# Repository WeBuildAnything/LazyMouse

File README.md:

# LazyMouse
Based on Arduino library [ESP32 BLE Combo Keyboard & Mouse](https://github.com/blackketter/ESP32-BLE-Combo.git) library by blackketter, which is a fork of T-vK Library.

The IMU sensor uses the [MPU6050 library by Electronic Cats](https://github.com/ElectronicCats/mpu6050.git).

Download and install these libraies before running the code.
# Features
1) Air Mouse with Left and Right Clicks 
2) Vertical and Horizontal Scrolling with Middle Click
3) Volume Control
4) Mute Key
5) Media Control (Play/Pause, Next, Previous)
6) Battery Voltage Sensing and Update every 15 mins

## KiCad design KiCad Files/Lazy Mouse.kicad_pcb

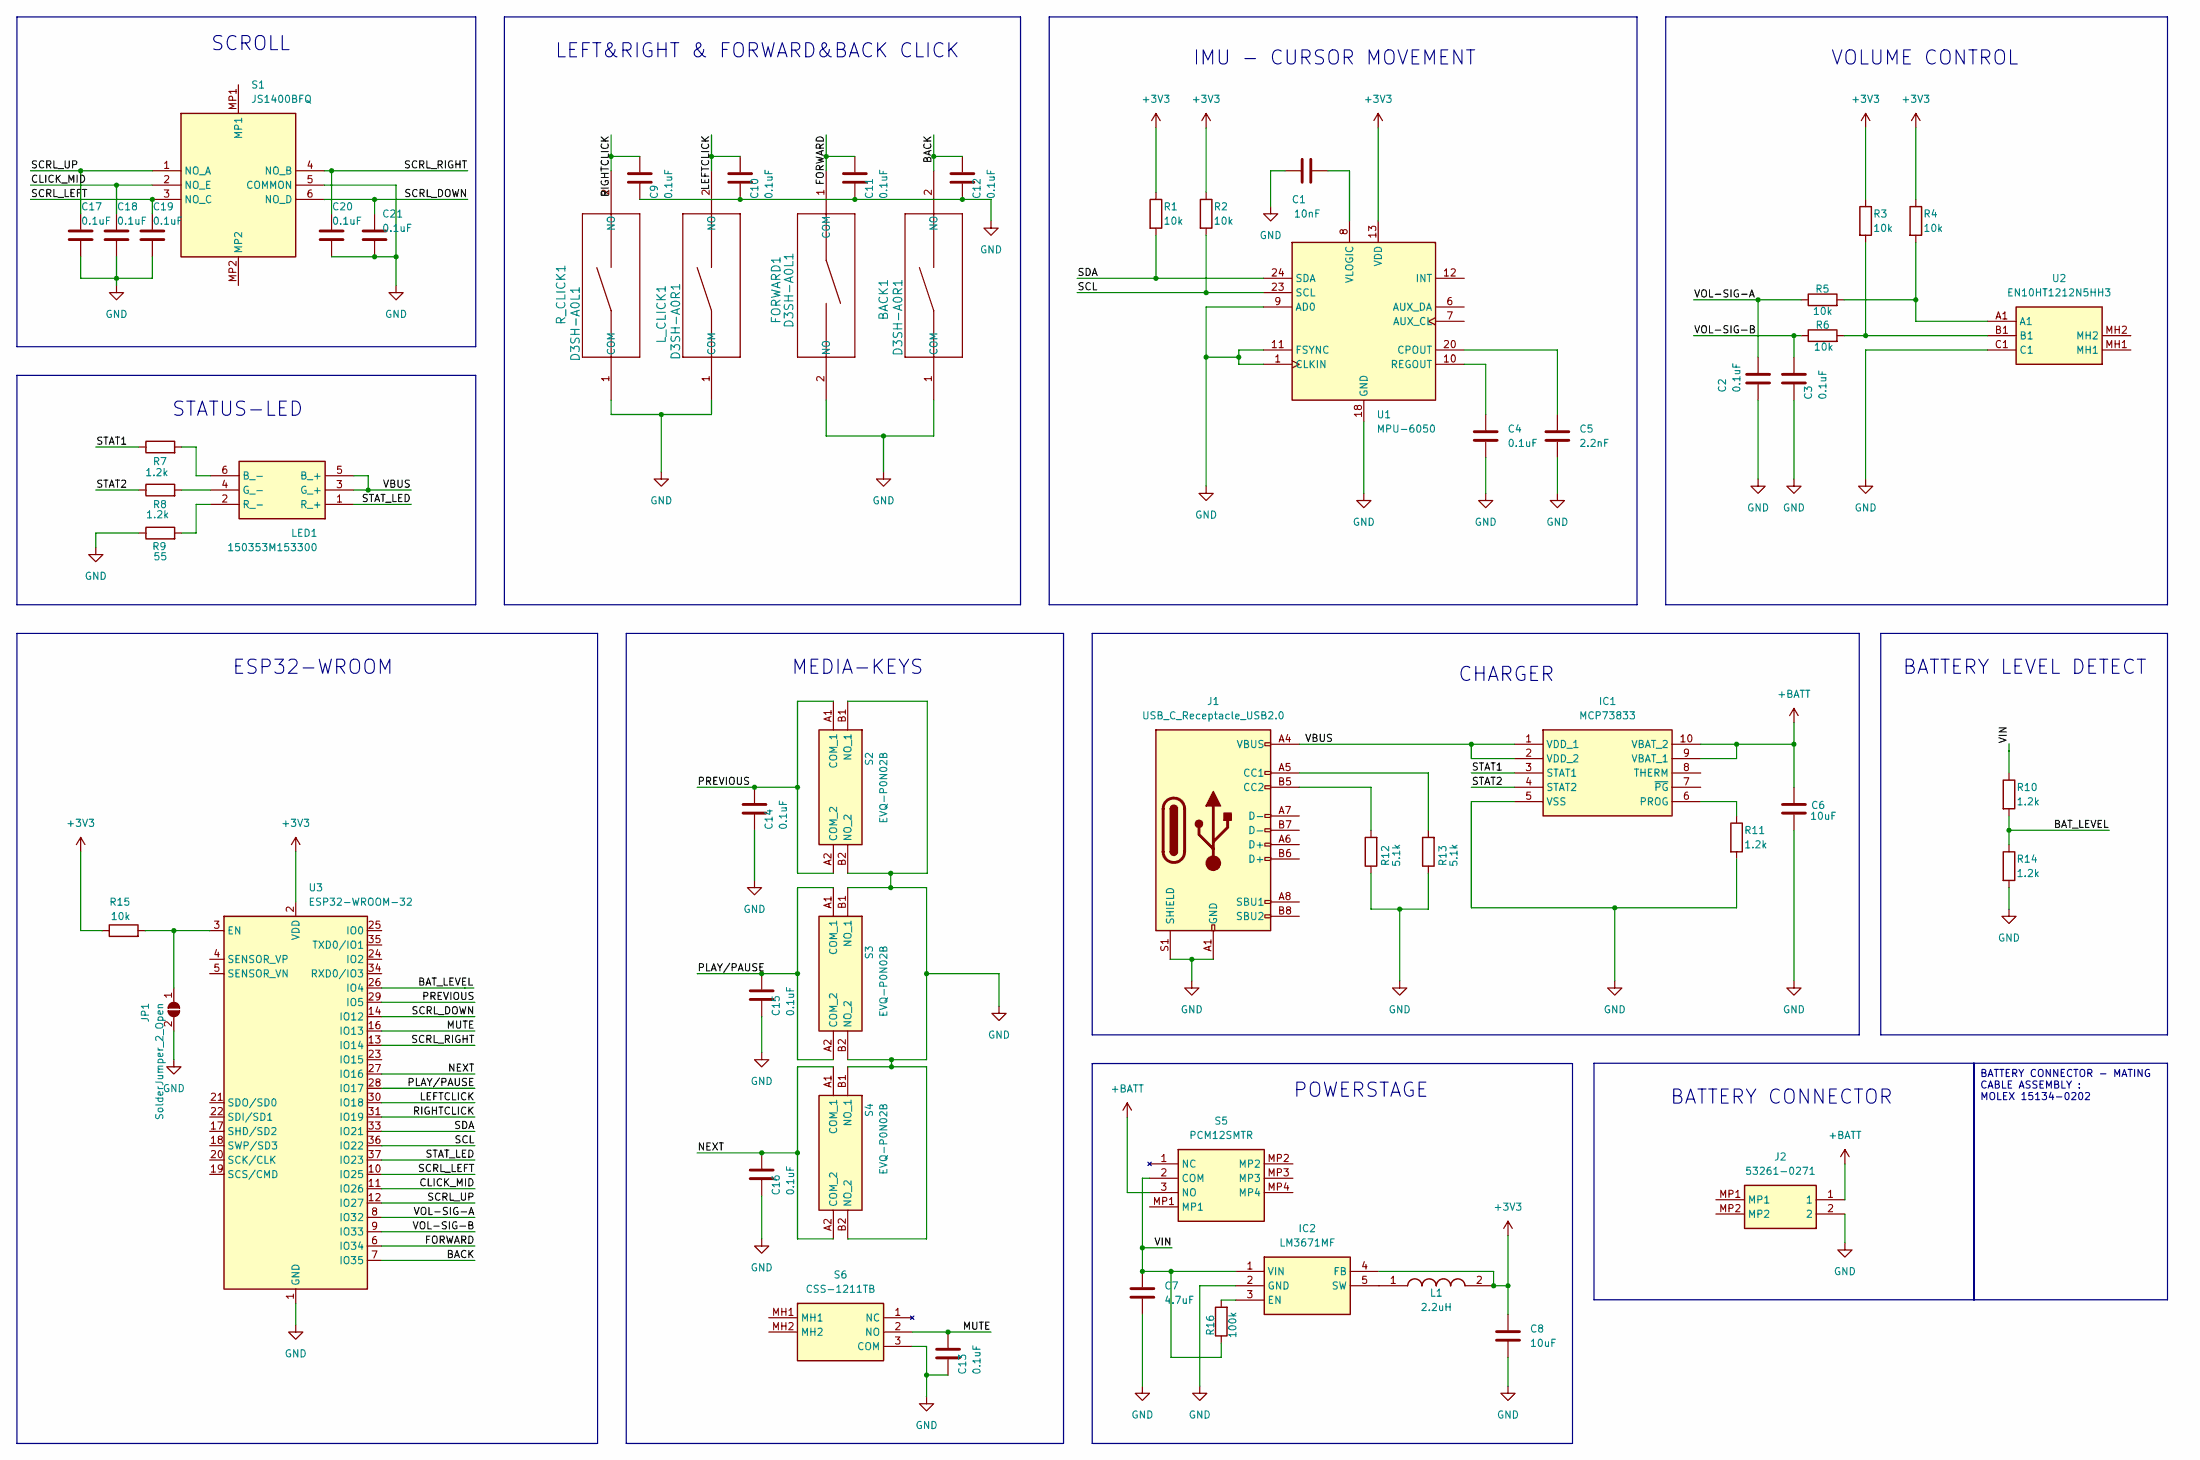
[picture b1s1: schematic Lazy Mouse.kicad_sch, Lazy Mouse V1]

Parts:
BACK1: D3SH-A0R1; D3SH-_0R1
C1: 10nF; C_0603_1608Metric
C2, C3, C4, C9, C10, C11, C12, C13, C14, C15, C16, C17, C18, C19, C20, C21: 0.1uF; C_0603_1608Metric
C5: 2.2nF; C_0603_1608Metric
C6, C8: 10uF; C_0603_1608Metric
C7: 4.7uF; C_0603_1608Metric
FORWARD1: D3SH-A0L1; D3SH-_0L1
IC1: MCP73833; SOP50P490X110-10N; Mouser Part Number 579-MCP73833-FCI/UN
IC2: LM3671MF; SOT95P280X145-5N; Mouser Part Number 926-LM3671MF125NOPB
J1: USB_C_Receptacle_USB2.0; USB_C_Receptacle_GCT_USB4105-xx-A_16P_TopMnt_Horizontal
J2: 53261-0271; 532610271; Mouser Part Number 538-53261-0271
JP1: SolderJumper_2_Open; SolderJumper-2_P1.3mm_Open_RoundedPad1.0x1.5mm
L1: 2.2uH; NRH2412T2R2MNGH; Mouser Part Number 963-NRH2412T2R2MNGH
LED1: 150353M153300; Mouser Part Number 710-150353M153300
L_CLICK1: D3SH-A0R1; D3SH-_0R1
R1, R2, R3, R4, R5, R6, R15: 10k; R_0603_1608Metric
R7, R8, R10, R11, R14: 1.2k; R_0603_1608Metric
R9: 55; R_0603_1608Metric
R12, R13: 5.1k; R_0603_1608Metric
R16: 100k; R_0603_1608Metric
R_CLICK1: D3SH-A0L1; D3SH-_0L1
S1: JS1400BFQ; Mouser Part Number 612-JS1400BFQ
S2, S3, S4: EVQ-P0N02B; EVQP0N02B; Mouser Part Number 667-EVQ-P0N02B
S5: PCM12SMTR; Mouser Part Number 611-PCM12SMTR
S6: CSS-1211TB; CSS1211TB; Manufacturer_Part_Number CSS-1211TB
U1: MPU-6050; InvenSense_QFN-24_4x4mm_P0.5mm
U2: EN10HT1212N5HH3; Mouser Part Number 858-EN10HT1212N5HH3
U3: ESP32-WROOM-32; ESP32-WROOM-32D

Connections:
+3V3: C8.1, IC2.4 (FB), L1.2, R1.1, R2.1, R3.1, R4.1, R15.1, U1.13 (VDD), U3.2 (VDD)
+BATT: C6.2, IC1.9 (VBAT_1), IC1.10 (VBAT_2), J2.1, S5.3 (NO)
/BACK: BACK1.2 (NO), C12.1, U3.7 (IO35)
/BAT_LEVEL: R10.2, R14.1, U3.26 (IO4)
/CLICK_MID: C18.1, S1.2 (NO_E), U3.11 (IO26)
/FORWARD: C11.1, FORWARD1.1 (COM), U3.6 (IO34)
/LEFTCLICK: C10.1, L_CLICK1.2 (NO), U3.30 (IO18)
/MUTE: C13.1, S6.2 (NO), U3.16 (IO13)
/NEXT: C16.1, S4.A1 (COM_1), S4.A2 (COM_2), U3.27 (IO16)
/PLAY/PAUSE: C15.1, S3.A1 (COM_1), S3.A2 (COM_2), U3.28 (IO17)
/PREVIOUS: C14.1, S2.A1 (COM_1), S2.A2 (COM_2), U3.29 (IO5)
/RIGHTCLICK: C9.1, R_CLICK1.2 (NO), U3.31 (IO19)
/SCL: R2.2, U1.23 (SCL), U3.36 (IO22)
/SCRL_DOWN: C21.1, S1.6 (NO_D), U3.14 (IO12)
/SCRL_LEFT: C19.1, S1.3 (NO_C), U3.10 (IO25)
/SCRL_RIGHT: C20.1, S1.4 (NO_B), U3.13 (IO14)
/SCRL_UP: C17.1, S1.1 (NO_A), U3.12 (IO27)
/SDA: R1.2, U1.24 (SDA), U3.33 (IO21)
/STAT1: IC1.3 (STAT1), R7.1
/STAT2: IC1.4 (STAT2), R8.1
/STAT_LED: LED1.1 (R_+), U3.37 (IO23)
/VBUS: IC1.1 (VDD_1), IC1.2 (VDD_2), J1.A4 (VBUS), J1.A9 (VBUS), J1.B4 (VBUS), J1.B9 (VBUS), LED1.3 (G_+), LED1.5 (B_+)
/VIN: C7.1, IC2.1 (VIN), R10.1, R16.1, S5.2 (COM)
/VOL-SIG-A: C2.1, R5.1, U3.8 (IO32)
/VOL-SIG-B: C3.1, R6.1, U3.9 (IO33)
GND: BACK1.1 (COM), C1.1, C2.2, C3.2, C4.2, C5.2, C6.1, C7.2, C8.2, C9.2, C10.2, C11.2, C12.2, C13.2, C14.2, C15.2, C16.2, C17.2, C18.2, C19.2, C20.2, C21.2, FORWARD1.2 (NO), IC1.5 (VSS), IC2.2 (GND), J1.A1 (GND), J1.A12 (GND), J1.B1 (GND), J1.B12 (GND), J1.S1 (SHIELD), J2.2, JP1.2 (B), L_CLICK1.1 (COM), R9.1, R11.2, R12.1, R13.1, R14.2, R_CLICK1.1 (COM), S1.5 (COMMON), S2.B1 (NO_1), S2.B2 (NO_2), S3.B1 (NO_1), S3.B2 (NO_2), S4.B1 (NO_1), S4.B2 (NO_2), S6.3 (COM), U1.1 (CLKIN), U1.9 (AD0), U1.11 (FSYNC), U1.18 (GND), U2.C1, U3.1 (GND), U3.15 (GND), U3.38 (GND), U3.39 (GND); also elsewhere on the board
unnamed: IC1.6 (PROG), R11.1
unnamed: IC2.3 (EN), R16.2
unnamed: IC2.5 (SW), L1.1
unnamed: J1.A5 (CC1), R13.2
unnamed: J1.B5 (CC2), R12.2
unnamed: JP1.1 (A), R15.2, U3.3 (EN)
unnamed: LED1.6 (B_-), R7.2
unnamed: LED1.4 (G_-), R8.2
unnamed: LED1.2 (R_-), R9.2
unnamed: R3.2, R6.2, U2.B1
unnamed: R4.2, R5.2, U2.A1
unnamed: C5.1, U1.20 (CPOUT)
unnamed: C4.1, U1.10 (REGOUT)
unnamed: C1.2, U1.8 (VLOGIC)

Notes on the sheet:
BATTERY CONNECTOR - MATING CABLE ASSEMBLY : MOLEX 15134-0202
VOLUME CONTROL
BATTERY LEVEL DETECT
MEDIA-KEYS
STATUS-LED
LEFT&RIGHT & FORWARD&BACK CLICK
BATTERY CONNECTOR
IMU - CURSOR MOVEMENT
POWERSTAGE
CHARGER
ESP32-WROOM
SCROLL

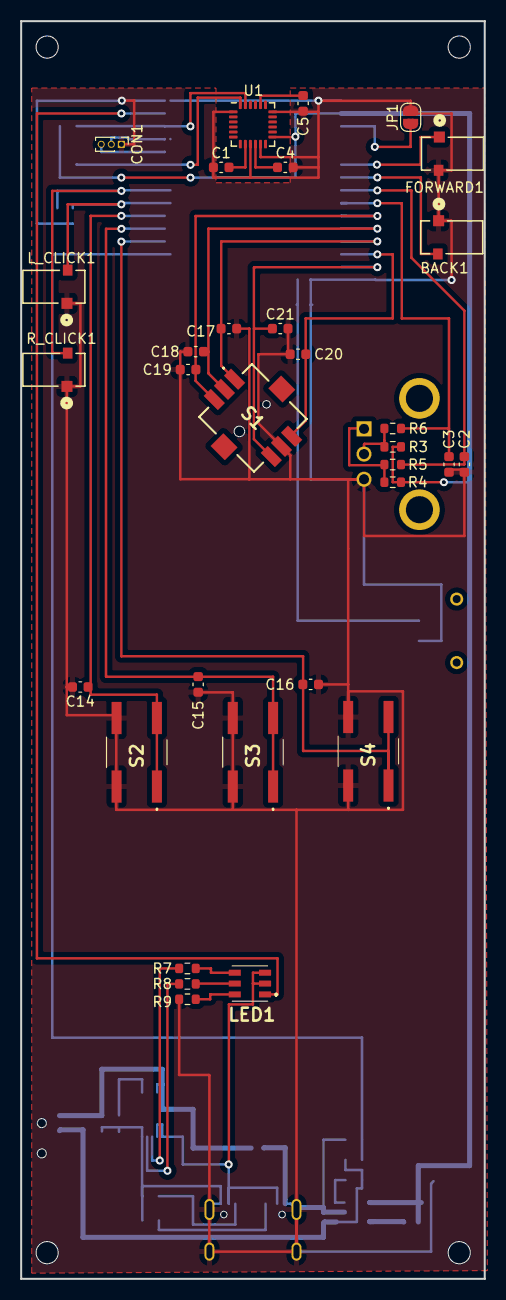
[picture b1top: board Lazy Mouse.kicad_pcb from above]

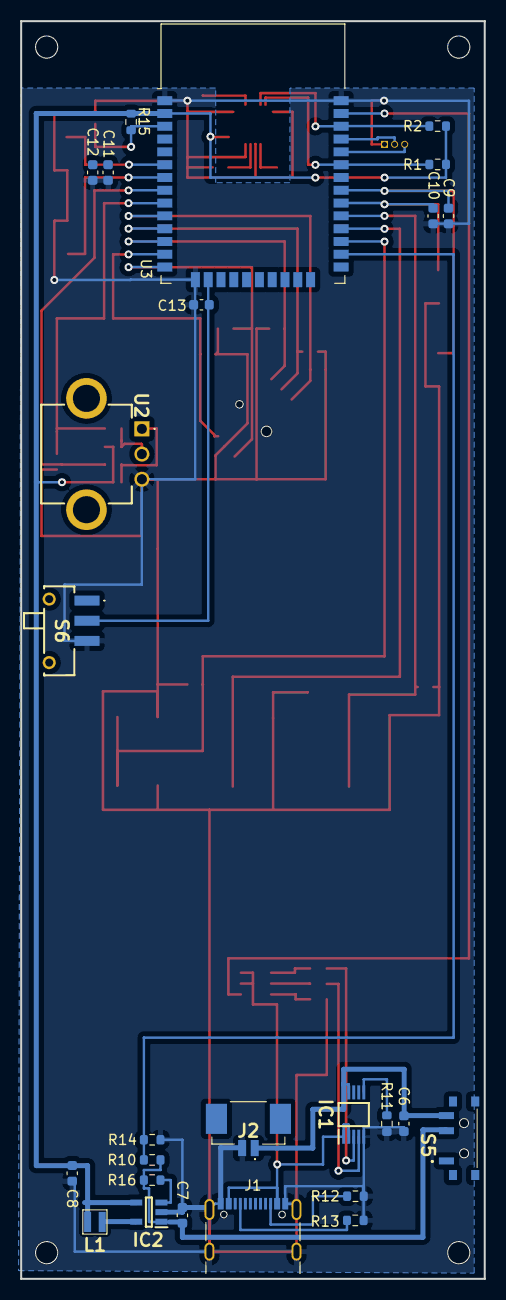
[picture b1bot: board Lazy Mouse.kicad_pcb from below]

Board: 2 copper layers, 46.0 x 124.8 mm, 62 parts (26 on the bottom side), 40 nets.

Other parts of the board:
CON1: PinHeader_1x03_P1.00mm_Vertical
H1, H2, H3, H4: MountingHole_2.2mm_M2

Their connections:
GND: CON1.1; also elsewhere on the board

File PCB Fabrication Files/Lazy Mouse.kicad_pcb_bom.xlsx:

designator | quantity | manufacturer | Mfg Part # | value | pack | mount_type
BACK1, L_CLICK1 | 2 | OMRON | D3SH-A0R1 | D3SH-A0R1 | D3SH-_0R1 | smt
C1 | 1 | MURATA | GRM188R72A103KA01J | 10nF | C_0603_1608Metric | smt
C10, C11, C12, C13, C14, C15, C16, C17, C18, C19, C2, C20, C21, C3, C4, C9 | 16 | MURATA | GRM188R72A104KA35J | 0.1uF | C_0603_1608Metric | smt
C5 | 1 | MURATA | GRM1885C2A222JA01D | 2.2nF | C_0603_1608Metric | smt
C6, C8 | 2 | MURATA | GRM188R61A106ME69J | 10uF | C_0603_1608Metric | smt
C7 | 1 | MURATA | GRM188R61C475KE11D | 4.7uF | C_0603_1608Metric | smt
CON1 | 1 |  |  | PinHeader_1x03_P1.00mm_Vertical | PinHeader_1x03_P1.00mm_Vertical | tht
FORWARD1, R_CLICK1 | 2 | OMROM | D3SH-A0L1 | D3SH-A0L1 | D3SH-_0L1 | smt
IC1 | 1 | MICROCHIP | MCP73833 | MCP73833 | SOP50P490X110-10N | smt
IC2 | 1 | TEXAS INSTRUMENTS | LM3671MF | LM3671MF | SOT95P280X145-5N | smt
J1 | 1 | GCT | USB4105-GF-A | USB_C_Receptacle_USB2.0 | USB_C_Receptacle_GCT_USB4105-xx-A_16P_TopMnt_Horizontal | smt
J2 | 1 | MOLEX | 53261-0271 | 53261-0271 | 532610271 | smt
L1 | 1 | TAIYO YUDEN | NRH2412T2R2MNGH | 2.2uH | NRH2412T2R2MNGH | smt
LED1 | 1 | WURTH ELECTRONICS | 150353M153300 | 150353M153300 | 150353M153300 | smt
R1, R15, R2, R3, R4, R5, R6 | 7 | PANASONIC | ERJ-S03J103V | 10k | R_0603_1608Metric | smt
R10, R11, R14, R7, R8 | 5 | PANASONIC | ERJ-P03J122V | 1.2k | R_0603_1608Metric | smt
R12, R13 | 2 | PANASONIC | ERJ-S03J512V | 5.1k | R_0603_1608Metric | smt
R16 | 1 | PANASONIC | ERJ-U03J104V | 100k | R_0603_1608Metric | smt
R9 | 1 | BOURNS | CR0603-FX-54R9ELF | 55 | R_0603_1608Metric | smt
S1 | 1 | E-SWITCH | JS1400BFQ | JS1400BFQ | JS1400BFQ | tht
S2, S3, S4 | 3 | PANASONIC | EVQ-P0N02B | EVQ-P0N02B | EVQP0N02B | smt
S5 | 1 | C&K SWITCHES | PCM12SMTR | PCM12SMTR | PCM12SMTR | tht
S6 | 1 | NIDEC | CSS-1211TB | CSS-1211TB | CSS1211TB | tht
U1 | 1 | TDK | MPU-6050 | MPU-6050 | InvenSense_QFN-24_4x4mm_P0.5mm | smt
U2 | 1 | TT ELECTRONICS | EN10HT1212N5HH3 | EN10HT1212N5HH3 | EN10HT1212N5HH3 | tht
U3 | 1 | ESPRESSIF | ESP32-WROOM-32E-N16 | ESP32-WROOM-32 Wireless Module | ESP32-WROOM-32D | smt

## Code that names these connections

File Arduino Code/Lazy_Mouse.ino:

#include <BleCombo.h>
#include <BleComboKeyboard.h>
#include <Wire.h>
#include <MPU6050.h>

#define BAT_LEVEL 4 //Analog IN
#define STAT_LED 23//Output

//Following pins are input_pullups
#define SCRL_UP 27
#define SCRL_DOWN 12
#define SCRL_RIGHT 14
#define SCRL_LEFT 25

#define CLICK_MID 26

#define LEFTCLICK 18
#define RIGHTCLICK 19

#define FORWARD 34
#define BACK 35

#define PLAY_PAUSE 17
#define NEXT 16
#define PREVIOUS 5

#define VOL_SIG_A 32
#define VOL_SIG_B 33
#define MUTE 13

int pins[] = {5, 12, 13, 14, 16,17,18,19,25,16,27,32,33,34,35};

MPU6050 mpu;
int16_t ax,ay,az,gx,gy,gz; //variable for IMU
int dx, dy; //mapped Variables

unsigned long previousMillis = 0;
const long interval = 900000;
unsigned long currentMillis;
volatile int lastEncoderA = LOW;
volatile int lastEncoderB = LOW;
float bat_volt;
int stat;

void setup()
{
  // put your setup code here, to run once:
  Wire.begin();
  mpu.initialize();
  Mouse.begin();
  Keyboard.begin();
  Serial.begin(115200);
  for(int i=0;i<15;i++)
  {
    pinMode(pins[i],INPUT_PULLUP);
  }
  attachInterrupt(digitalPinToInterrupt(VOL_SIG_A), updateVolume, CHANGE);
  attachInterrupt(digitalPinToInterrupt(VOL_SIG_B), updateVolume, CHANGE);
  bat_volt = (analogRead(BAT_LEVEL)/4095)*3.3;
  stat = map(bat_volt,3,4.2,0,100);
  Keyboard.setBatteryLevel(stat);
}

void loop() {
  currentMillis = millis();
  if(Keyboard.isConnected())
  {
   currentMillis = millis();
    if (currentMillis - previousMillis >= interval)
      {
      previousMillis = currentMillis;
      bat_volt = (analogRead(BAT_LEVEL)/4095)*3.3;
      stat = map(bat_volt,3,4.2,0,100);
      Keyboard.setBatteryLevel(stat);
      }
   //Connected Status
   digitalWrite (STAT_LED,HIGH);
   //Cursor_Move
   mpu.getMotion6(&ax, &ay, &az, &gx, &gy, &gz);
   dx=(gx+260)/150;
   dy=(gy+260)/150;
   Mouse.move(dx,dy);
   //Mouse Funtions
   if (digitalRead(LEFTCLICK) == LOW){
      Mouse.press(MOUSE_LEFT);}
   if (digitalRead(LEFTCLICK) == HIGH) {
      Mouse.release(MOUSE_LEFT);}
   if (digitalRead(RIGHTCLICK) == LOW){
      Mouse.press(MOUSE_RIGHT);}
   if (digitalRead(RIGHTCLICK) == HIGH) {
      Mouse.release(MOUSE_RIGHT);}
   if (digitalRead(CLICK_MID) == LOW){
      Mouse.press(MOUSE_MIDDLE);}
   if (digitalRead(CLICK_MID) == HIGH){
     Mouse.release(MOUSE_MIDDLE);}
   if (digitalRead(FORWARD) == LOW){
     Mouse.click(MOUSE_FORWARD);}
   if (digitalRead(BACK) == LOW){
     Mouse.click(MOUSE_BACK);}
   if (digitalRead(BACK) == LOW){
     Mouse.click(MOUSE_BACK);}
    if (digitalRead(SCRL_UP) == LOW){
     Mouse.move(0,0,1);}
    if (digitalRead(SCRL_DOWN) == LOW){
     Mouse.move(0,0,-1);}
    if (digitalRead(SCRL_RIGHT) == LOW){
     Mouse.move(0,0,0,1);}
    if (digitalRead(SCRL_LEFT) == LOW){
     Mouse.move(0,0,0,-1);} 
    //Media Control
    if (digitalRead(MUTE) == LOW){
     Keyboard.write(KEY_MEDIA_MUTE);}
    if (digitalRead(PLAY_PAUSE) == LOW){
     Keyboard.write(KEY_MEDIA_PLAY_PAUSE);}
    if (digitalRead(NEXT) == LOW){
     Keyboard.write(KEY_MEDIA_NEXT_TRACK);}
    if (digitalRead(PREVIOUS) == LOW){
     Keyboard.write(KEY_MEDIA_PREVIOUS_TRACK);}
  }
  //Blink LED if Bluetooth Disconnected
  else
  {
    digitalWrite(STAT_LED,LOW);
    digitalWrite(STAT_LED,HIGH);
    delay(500);
    digitalWrite(STAT_LED,LOW);
    delay(500);
  }
}

void updateVolume(){
  int encoderA = digitalRead(VOL_SIG_A);
  int encoderB = digitalRead(VOL_SIG_B);
  
  if ((lastEncoderA == LOW && encoderA == HIGH) || (lastEncoderB == LOW && encoderB == HIGH))
    {
    // Clockwise rotation
    Keyboard.write(KEY_MEDIA_VOLUME_UP);
    Serial.println("VolumeUp");
    }   
  else if ((lastEncoderA == HIGH && encoderA == LOW) || (lastEncoderB == HIGH && encoderB == LOW))
    {
    // Counterclockwise rotation
    Keyboard.write(KEY_MEDIA_VOLUME_DOWN);
    Serial.println("Volume Down");
    }
  lastEncoderA = encoderA;
  lastEncoderB = encoderB;
}
